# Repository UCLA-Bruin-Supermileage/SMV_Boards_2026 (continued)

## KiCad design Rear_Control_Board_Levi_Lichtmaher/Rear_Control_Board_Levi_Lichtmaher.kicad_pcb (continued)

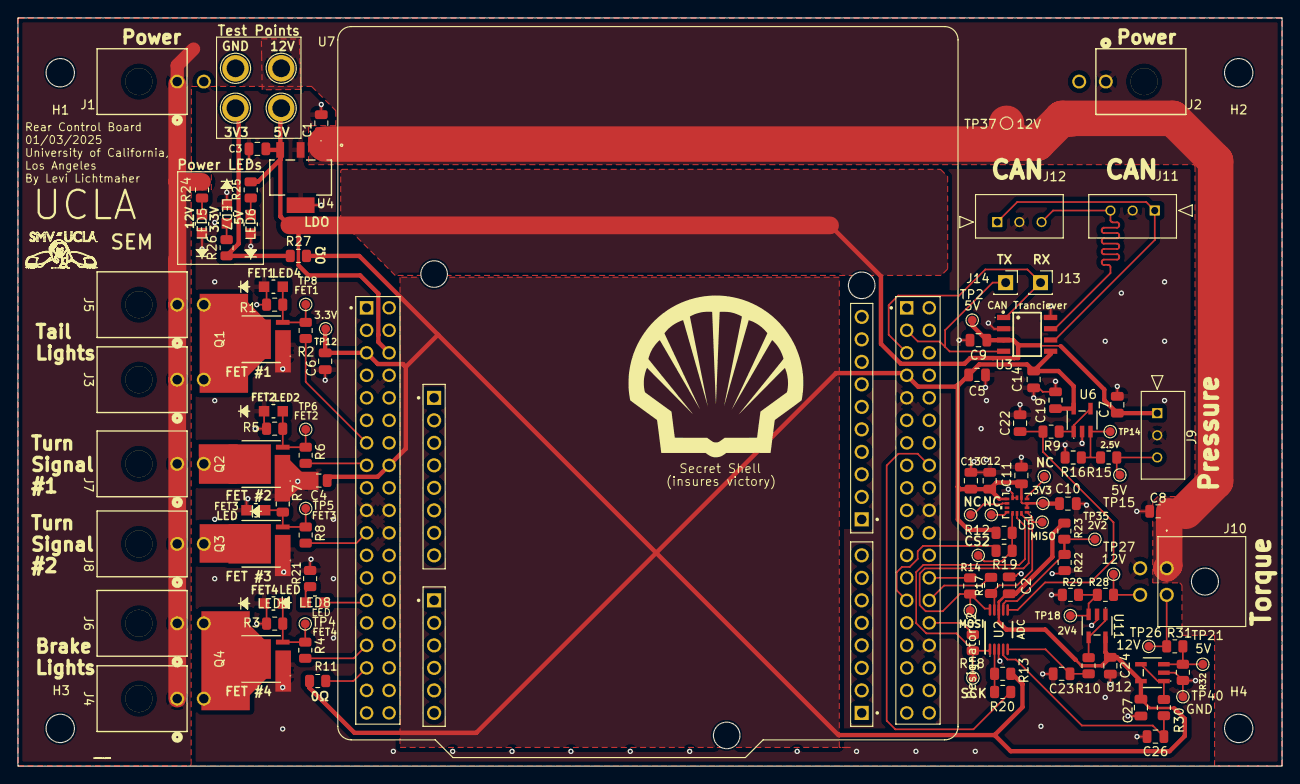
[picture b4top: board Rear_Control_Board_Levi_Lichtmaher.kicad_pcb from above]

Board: 2 copper layers, 142.7 x 84.4 mm, 117 parts (0 on the bottom side), 50 nets.

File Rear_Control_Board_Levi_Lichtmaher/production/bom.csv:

Designator,Footprint,Quantity,Value,LCSC Part #
"C1, C12, C14, C2, C22, C23, C26, C3, C4, C5, C6, C8, C9",0805,13,0.1uF,
"C10, C11, C19, C24, C27, C7",0805,6,0.1 uF,
C13,0805,1,10uF,
"J1, J2, J3, J4, J5, J6, J7, J8",CONN_SD-43045-001_02_MOL,8,430450200,
J10,4_pin0430450401,1,Molex Micro-Fit 4 Pin,
"J11, J12, J9",3pin_CON_22035035_MOL,3,22035035,
"J13, J14",PinSocket_1x01_P2.54mm_Vertical,2,Conn_01x01_Socket,
"LED1, LED2, LED3, LED4, LED5, LED6, LED7, LED8",LED_LTST-C170GKT_LTO,8,LTST-C170GKT,
"Q1, Q2, Q3, Q4",LFPAK56_SOT669_NEX-mosfet,4,PSMN1R8-40YLC_115,
"R1, R12, R13, R15, R16, R23, R29, R3, R32, R5, R7",0805,11,10k,
"R10, R30, R9",0805,3,100,
"R11, R27",0805,2,0,
"R14, R17, R18, R19, R20",0805,5,50,
"R2, R24, R4, R6, R8",0805,5,1K,
R21,0805,1,150,
R22,0805,1,20K,
R25,0805,1,300,
R26,0805,1,220,
"R28, R31",0805,2,40k,
TP1,TestPoint_Pad_D1.0mm,1,3.3V,
TP10,TestPoint_Plated_Hole_D2.0mm,1,3V3,
TP11,TestPoint_Plated_Hole_D2.0mm,1,GND,
TP12,TestPoint_Pad_D1.0mm,1,3V3,
"TP13, TP17, TP23",TestPoint_Pad_D1.0mm,3,NC,
TP14,TestPoint_Pad_D1.0mm,1,2V5,
TP15,TestPoint_Pad_D1.0mm,1,5V Pressure Sensor,
"TP18, TP21",TestPoint_Pad_D1.0mm,2,2.4V,
TP19,TestPoint_Pad_D1.0mm,1,CS2,
TP2,TestPoint_Pad_D1.0mm,1,5V,
TP20,TestPoint_Pad_D1.0mm,1,MOSI,
TP22,TestPoint_Pad_D1.0mm,1,SCK,
TP26,TestPoint_Pad_D1.0mm,1,12V Torque_P,
TP27,TestPoint_Pad_D1.0mm,1,12V Torque_N,
TP3,TestPoint_Pad_D1.0mm,1,MISO,
TP35,TestPoint_Pad_D1.0mm,1,2V2,
TP37,TestPoint_Pad_D1.0mm,1,12V,
TP4,TestPoint_Pad_D1.0mm,1,Mosfet #4,
TP40,TestPoint_Pad_D1.0mm,1,GND,
TP5,TestPoint_Pad_D1.0mm,1,Mosfet #3,
TP6,TestPoint_Pad_D1.0mm,1,Mosfet #2,
TP7,TestPoint_Plated_Hole_D2.0mm,1,5V,
TP8,TestPoint_Pad_D1.0mm,1,Mosfet #1,
TP9,TestPoint_Plated_Hole_D2.0mm,1,12V,
"U11, U12, U6",SOT-23-5_MC_MCH,3,MCP6286T-E/OT,
U2,DGS0010A_N,1,ADS1118QDGSRQ1,
U3,SOIC127P600X175-8N,1,MCP2562-E/P,
U4,DCY4_TEX,1,UA78M05QDCYRG4Q1,
U5,QFN_LHHXTR_STM,1,ASM330LHHTR,

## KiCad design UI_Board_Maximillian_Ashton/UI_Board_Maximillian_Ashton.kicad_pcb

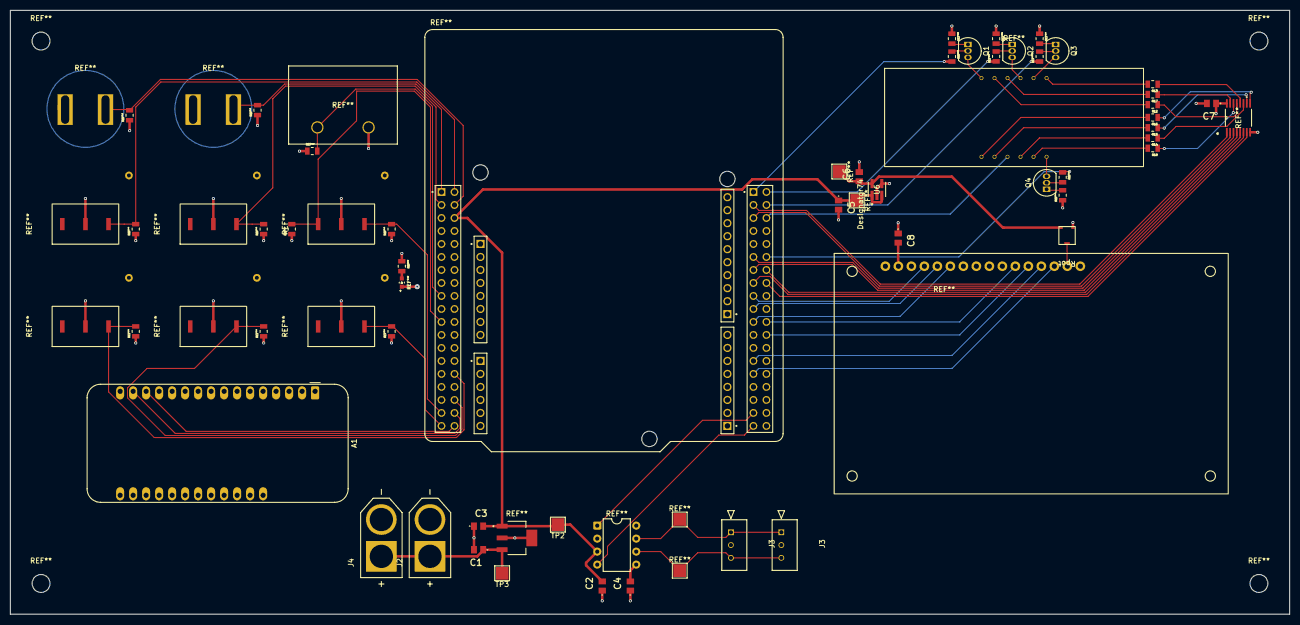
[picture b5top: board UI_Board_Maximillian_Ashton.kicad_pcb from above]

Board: 4 copper layers, 250.0 x 118.0 mm, 28 parts (0 on the bottom side), 7 nets.

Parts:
A1: Adafruit_Feather_HUZZAH32_ESP32; Adafruit_Feather
C1, C2, C3, C4, C5, C6, C7, C8: 0.1uF,50V; Cap0805
J2, J4: XT60-M; AMASS_XT60-M
J3, J3#2: 22035035; 3pin_CON_22035035_MOL
Q1, Q2, Q3, Q4: 2N3904; TO-92_Inline
R12, R13, R14, R15, R16, R17, R18: 220 ohms, 0.0625 watts; 0805RESC2012X60N
Rpot: 10K Ohms, 0.125 watts; 3313J-2-103E Pot
TP2, TP3: TestPoint2.5x2.5mm; TestPoint_Pad_2.5x2.5mm
U6: TPS7A2030PDBVR; DBV0005A-IPC_A

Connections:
+3.3V: A1.2 (3V3), C4.2, C7.1, C8.2
+3V0: C6.1, Rpot.3, U6.5 (OUT)
+5V: C2.2, C3.2, C5.1, TP2.1, U6.1 (IN), U6.3 (EN)
+12V: C1.1, J2.P (POS), J4.P (POS), TP3.1
/CANH: J3.1, J3#2.1
/CANL: J3.3, J3#2.3
GND: A1.4 (GND), C1.2, C2.1, C3.1, C4.1, C5.2, C6.2, C7.2, C8.1, J2.N (NEG), J3.2, J3#2.2, J4.N (NEG), Rpot.2, U6.2 (GND), U6.4 (NC)
